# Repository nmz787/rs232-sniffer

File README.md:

rs232-sniffer
=============

I needed a microcontroller-controlled RS-232 serial mouse, and had an Arduino Mega 2560 laying around.

Files are in KiCad format, the Arduino shield outline and placement was based on the Eagle file supplied by Arduino and converted by the script (https://github.com/DanChianucci/Eagle2Kicad).

All 8 RS-232 pins are accounted for, not just RX and TX.

You can see and order a board from OSHpark here:
(https://oshpark.com/shared_projects/Vs4zWf41)

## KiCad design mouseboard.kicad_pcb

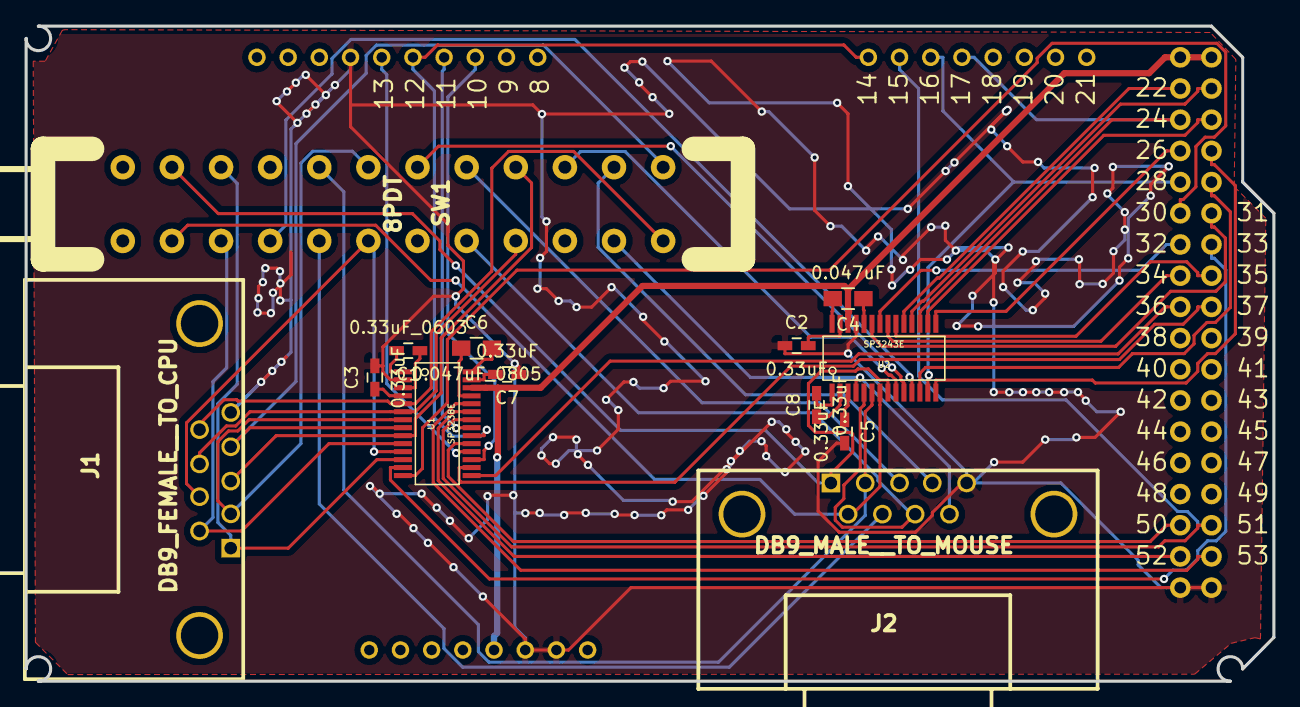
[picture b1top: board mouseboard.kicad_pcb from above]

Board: 2 copper layers, 101.6 x 53.3 mm, 17 parts (0 on the bottom side), 57 nets.

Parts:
C1: 0.33uF_0603; C_0603_HandSoldering
C2, C3, C5, C7, C8: 0.33uF; C_0603_HandSoldering
C4: 0.047uF; C_0805_HandSoldering
C6: 0.047uF_0805; C_0805_HandSoldering
COMMUNICATION1: CONN_01X08; 1X08
J1: DB9_FEMALE__TO_CPU; DB9FC
J2: DB9_MALE__TO_MOUSE; DB9MC
JP6: CONN_01X10; 1X10
POWER1: CONN_01X08; 1X08
SW1: 8PDT
U1: SP3238E; TSSOP-28
U2: SP3243E; TSSOP-28
XIO1: CONN_02X18; 2X18

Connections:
/CD_FROM_MOUSE: J2.1, SW1.22, U2.8
/CD_TO_CPU: J1.1, SW1.20, U1.12
/CTS_FROM_MOUSE: J2.8, SW1.9, U2.5
/CTS_TO_CPU: J1.8, SW1.7, U1.6
/DSR_FROM_MOUSE: J2.6, SW1.21, U2.7
/DSR_TO_CPU: J1.6, SW1.19, U1.10
/DTR_FROM_CPU: J1.4, SW1.2, U1.8
/DTR_FROM_MCU: SW1.6, U2.9
/DTR_TO_MOUSE: J2.4, SW1.4
/RI_FROM_MOUSE: J2.9, SW1.3, U2.4
/RI_TO_CPU: J1.9, SW1.1, U1.5
/RTS_FROM_CPU: J1.7, SW1.13, U1.11
/RTS_FROM_MCU: SW1.17, U2.11
/RTS_TO_MOUSE: J2.7, SW1.15
/RX_FROM_MOUSE: J2.2, SW1.16, U2.6
/RX_TO_CPU: J1.2, SW1.14, U1.7
/TX_FROM_CPU: J1.3, SW1.8, U1.9
/TX_FROM_MCU: SW1.12, U2.10
/TX_TO_MOUSE: J2.3, SW1.10
/c1_1_minus: C6.1, U1.25
/c1_2_pos: C4.2, U2.28
/c2_1_minus: C1.1, U1.3
/c2_2_neg: C8.1, U2.2
CPU_ONLINE: U1.13, XIO1.14
CPU_SHUTDOWN: U1.14, XIO1.11
CPU_STATUS: U1.15, XIO1.17
GND: C2.1, C3.2, C5.2, C7.1, J1.5, J2.5, JP6.4, POWER1.6, POWER1.7, U1.2, U2.25, XIO1.35, XIO1.36
MOUSE_ONLINE: U2.23, XIO1.12
MOUSE_SHUTDOWN: U2.22, XIO1.13
MOUSE_STATUS: U2.21, XIO1.15
unnamed: C1.2, U1.1
unnamed: C2.2, U2.27
unnamed: C3.1, U1.4
unnamed: C4.1, U2.24
unnamed: C5.1, U2.3
unnamed: C6.2, U1.28
unnamed: C7.2, U1.27
unnamed: C8.2, U2.1
PWR: POWER1.5, U1.26, U2.26, XIO1.1, XIO1.2
TTL_CD_FROM_MOUSE: U2.15, XIO1.7
TTL_CD_TO_CPU: JP6.8, U1.17
TTL_CTS_FROM_MOUSE: U2.18, XIO1.4
TTL_CTS_FROM_MOUSE-_: U2.20, XIO1.16
TTL_CTS_TO_CPU: U1.23, XIO1.33
TTL_DSR_FROM_MOUSE: U2.16, XIO1.6
TTL_DSR_TO_CPU: U1.19, XIO1.31
TTL_DTR_FROM_CPU: JP6.7, U1.21
TTL_DTR_FROM_CPU-_: U1.16, XIO1.18
TTL_DTR_TO_MOUSE: U2.14, XIO1.8
TTL_RI_FROM_MOUSE: U2.19, XIO1.3
TTL_RI_TO_CPU: U1.24, XIO1.34
TTL_RTS_FROM_CPU: JP6.5, U1.18
TTL_RTS_TO_MOUSE: U2.12, XIO1.10
TTL_RX_FROM_MOUSE: COMMUNICATION1.5, U2.17, XIO1.5
TTL_RX_TO_CPU: COMMUNICATION1.7, U1.22, XIO1.32
TTL_TX_FROM_CPU: COMMUNICATION1.8, JP6.6, U1.20
TTL_TX_TO_MOUSE: COMMUNICATION1.6, U2.13, XIO1.9

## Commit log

2014-11-30 updated readme with OSHpark link
